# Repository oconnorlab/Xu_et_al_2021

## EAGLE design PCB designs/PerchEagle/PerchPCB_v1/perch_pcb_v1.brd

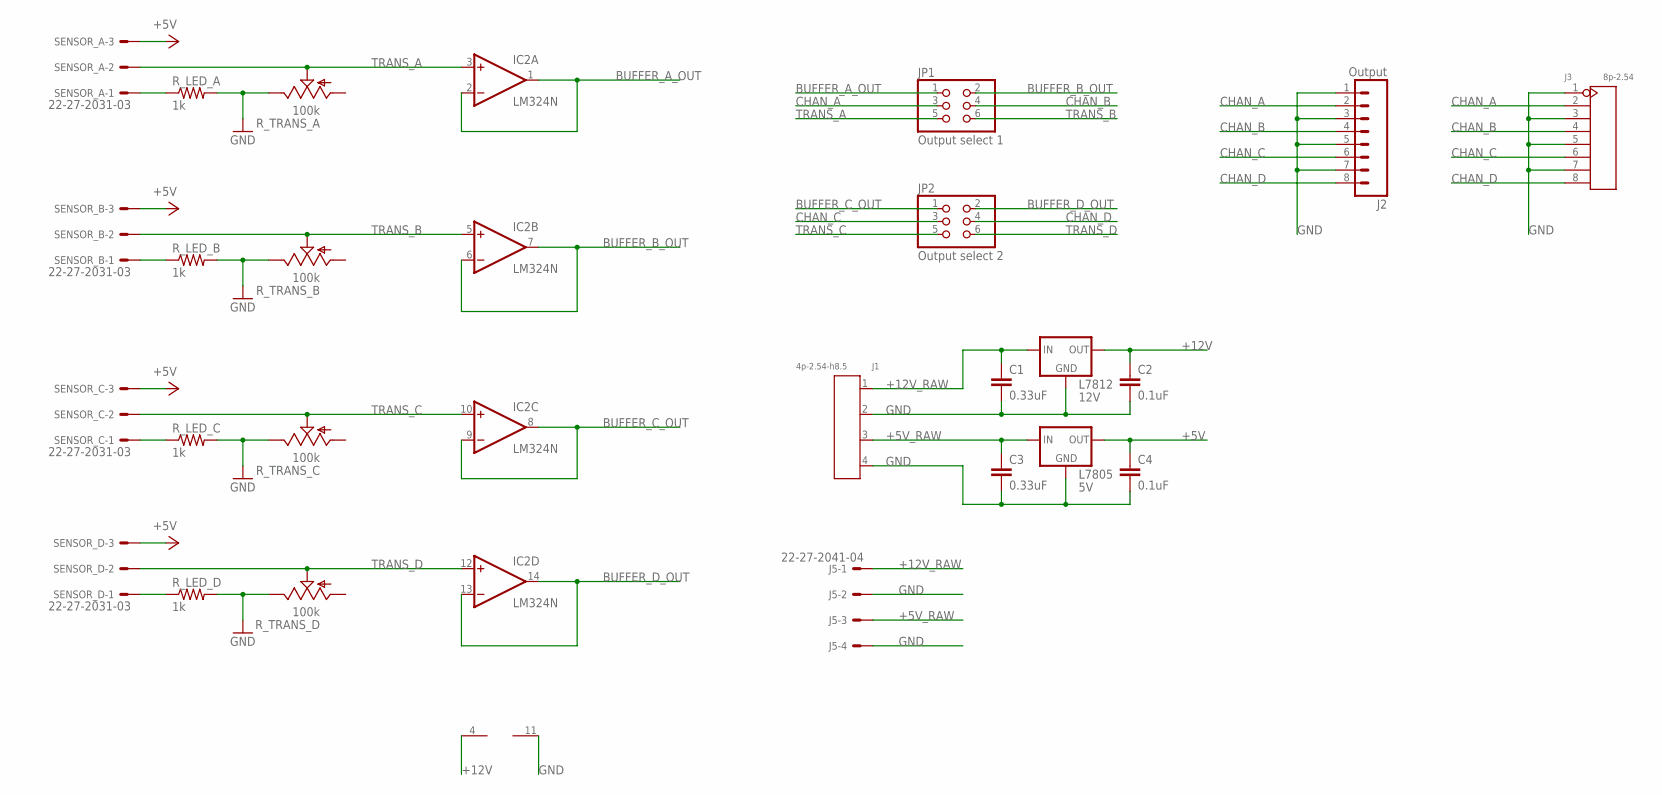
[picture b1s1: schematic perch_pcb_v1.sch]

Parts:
C1, C3: 0.33uF; CAP-PTH-SMALL
C2, C4: 0.1uF; CAP-PTH-SMALL
IC2: LM324N; DIL14
J1: 4p-2.54-h8.5; H4-2.54-8.52X6.3MM
J2: Output; 1X08_ROUND
J3: 8p-2.54; H8-2.54-18.7X6.3MM
J5: 22-27-2041-04; 6410-04
JP1: Output select 1; 2X03
JP2: Output select 2; 2X03
L7805: 5V; TO220-IGO
L7812: 12V; TO220-IGO
R_LED_A: 1k; AXIAL-0.3
R_LED_B: 1k; AXIAL-0.3
R_LED_C: 1k; AXIAL-0.3
R_LED_D: 1k; AXIAL-0.3
R_TRANS_A: 100k; B64W
R_TRANS_B: 100k; B64W
R_TRANS_C: 100k; B64W
R_TRANS_D: 100k; B64W
SENSOR_A: 22-27-2031-03; 6410-03
SENSOR_B: 22-27-2031-03; 6410-03
SENSOR_C: 22-27-2031-03; 6410-03
SENSOR_D: 22-27-2031-03; 6410-03

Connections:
+5V: C4.1, L7805.OUT, SENSOR_A.3, SENSOR_B.3, SENSOR_C.3, SENSOR_D.3
+5V_RAW: C3.1, J1.3, J5.3, L7805.IN
+12V: C2.1, IC2.4 (V+), L7812.OUT
+12V_RAW: C1.1, J1.1, J5.1, L7812.IN
BUFFER_A_OUT: IC2.1 (OUT), IC2.2 (-IN), JP1.1
BUFFER_B_OUT: IC2.6 (-IN), IC2.7 (OUT), JP1.2
BUFFER_C_OUT: IC2.8 (OUT), IC2.9 (-IN), JP2.1
BUFFER_D_OUT: IC2.13 (-IN), IC2.14 (OUT), JP2.2
CHAN_A: J2.2, J3.2, JP1.3
CHAN_B: J2.4, J3.4, JP1.4
CHAN_C: J2.6, J3.6, JP2.3
CHAN_D: J2.8, J3.8, JP2.4
GND: C1.2, C2.2, C3.2, C4.2, IC2.11 (V-), J1.2, J1.4, J2.1, J2.3, J2.5, J2.7, J3.1, J3.3, J3.5, J3.7, J5.2, J5.4, L7805.GND, L7812.GND, R_LED_A.P$2 (2), R_LED_B.P$2 (2), R_LED_C.P$2 (2), R_LED_D.P$2 (2), R_TRANS_A.E, R_TRANS_B.E, R_TRANS_C.E, R_TRANS_D.E
unnamed: R_LED_B.P$1 (1), SENSOR_B.1
unnamed: R_LED_A.P$1 (1), SENSOR_A.1
unnamed: R_LED_C.P$1 (1), SENSOR_C.1
unnamed: R_LED_D.P$1 (1), SENSOR_D.1
TRANS_A: IC2.3 (+IN), JP1.5, R_TRANS_A.S, SENSOR_A.2
TRANS_B: IC2.5 (+IN), JP1.6, R_TRANS_B.S, SENSOR_B.2
TRANS_C: IC2.10 (+IN), JP2.5, R_TRANS_C.S, SENSOR_C.2
TRANS_D: IC2.12 (+IN), JP2.6, R_TRANS_D.S, SENSOR_D.2

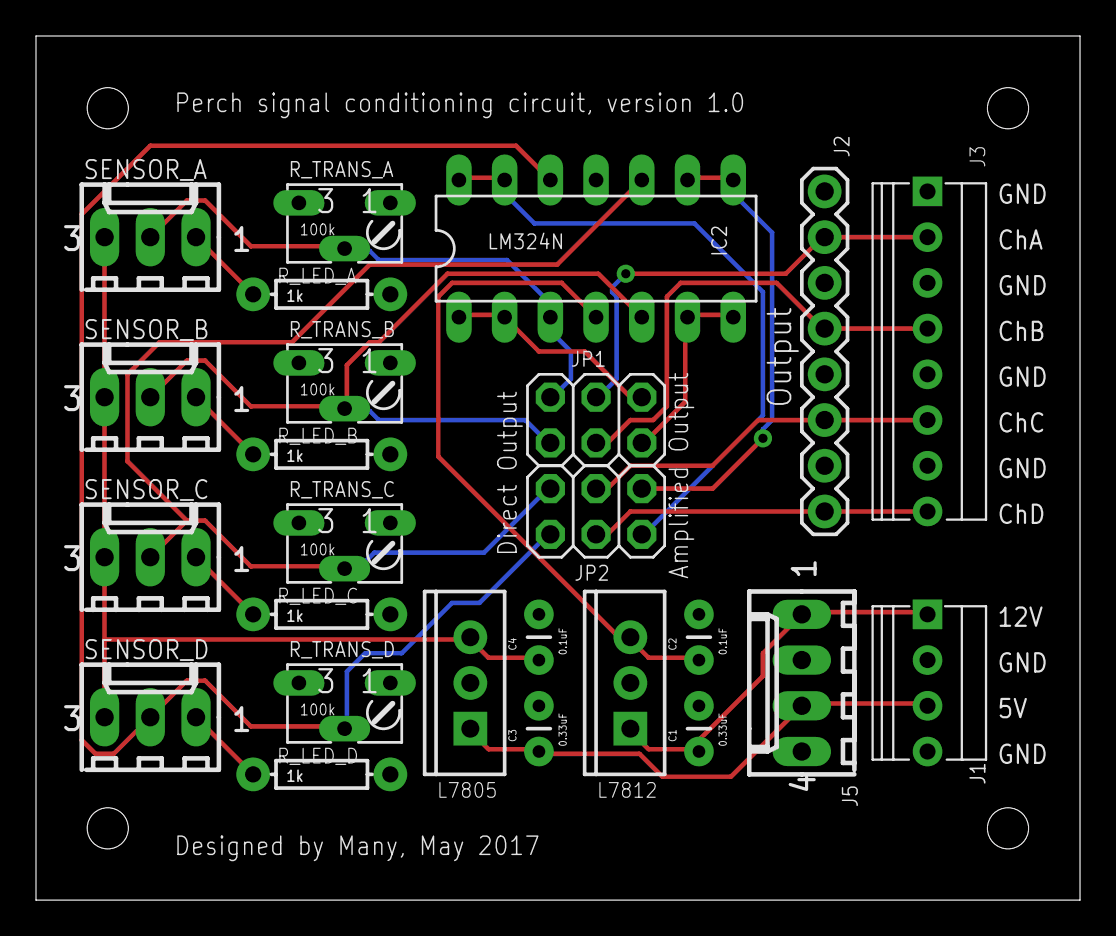
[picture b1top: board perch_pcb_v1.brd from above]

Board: 2 copper layers, 58.0 x 48.0 mm, 25 parts (0 on the bottom side), 21 nets.

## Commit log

2021-11-11 Initial commit
    Copy relevant code from lab1 and seqlick
2023-03-26 Add relevant CAD files

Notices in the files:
parts and their libraries:
SparkFun-Passives: Licensing: Creative Commons ShareAlike 4.0 International - https://creativecommons.org/licenses/by-sa/4.0
